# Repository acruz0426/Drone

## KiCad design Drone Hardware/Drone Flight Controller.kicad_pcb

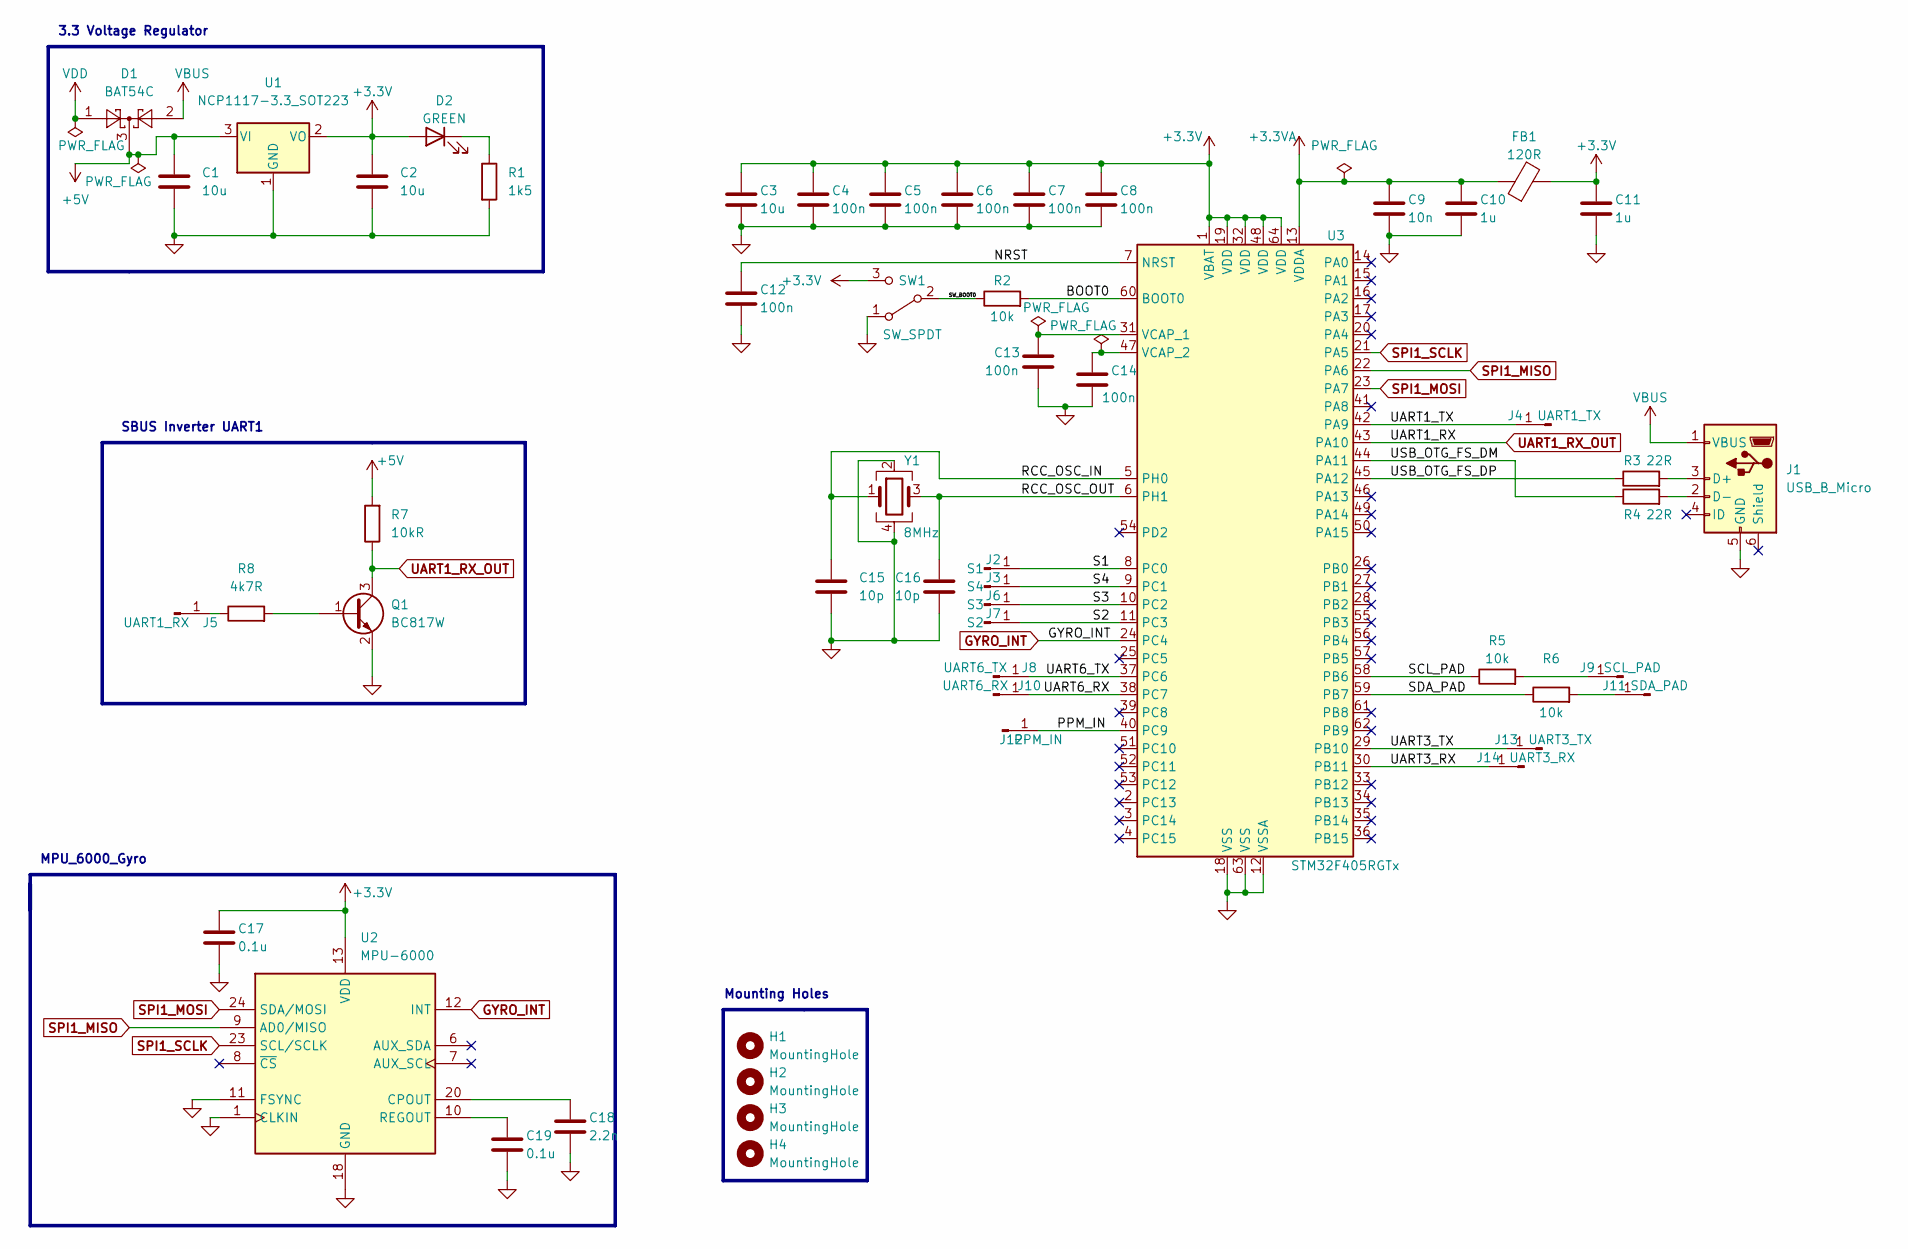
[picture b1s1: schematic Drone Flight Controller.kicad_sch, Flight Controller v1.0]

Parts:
C1, C2, C3: 10u; C_0805_2012Metric
C4, C5, C6, C7, C8, C12, C13, C14: 100n; C_0402_1005Metric
C9: 10n; C_0402_1005Metric
C10, C11: 1u; C_0402_1005Metric
C15, C16: 10p; C_0402_1005Metric
C17, C19: 0.1u; C_0402_1005Metric
C18: 2.2n; C_0402_1005Metric
D1: BAT54C; SOT-23
D2: GREEN; LED_0603_1608Metric
FB1: 120R; L_0603_1608Metric
H1, H2, H3, H4: MountingHole; MountingHole_2.2mm_M2
J1: USB_B_Micro; USB_Micro-B_Wuerth_629105150521
J2: S1; SolderWirePad_1x01_SMD_1x2mm
J3: S4; SolderWirePad_1x01_SMD_1x2mm
J4: UART1_TX; SolderWirePad_1x01_SMD_1x2mm
J5: UART1_RX; SolderWirePad_1x01_SMD_1x2mm
J6: S3; SolderWirePad_1x01_SMD_1x2mm
J7: S2; SolderWirePad_1x01_SMD_1x2mm
J8: UART6_TX; SolderWirePad_1x01_SMD_1x2mm
J9: SCL_PAD; SolderWirePad_1x01_SMD_1x2mm
J10: UART6_RX; SolderWirePad_1x01_SMD_1x2mm
J11: SDA_PAD; SolderWirePad_1x01_SMD_1x2mm
J12: PPM_IN; SolderWirePad_1x01_SMD_1x2mm
J13: UART3_TX; SolderWirePad_1x01_SMD_1x2mm
J14: UART3_RX; SolderWirePad_1x01_SMD_1x2mm
Q1: BC817W; SOT-323_SC-70
R1: 1k5; R_0402_1005Metric
R2, R5, R6: 10k; R_0402_1005Metric
R3, R4: 22R; R_0402_1005Metric
R7: 10kR; R_0402_1005Metric
R8: 4k7R; R_0402_1005Metric
SW1: SW_SPDT; SW_DIP_SPSTx01_Slide_Copal_CVS-01xB_W5.9mm_P1mm
U1: NCP1117-3.3_SOT223; SOT-223-3_TabPin2
U2: MPU-6000; InvenSense_QFN-24_4x4mm_P0.5mm
U3: STM32F405RGTx; LQFP-64_10x10mm_P0.5mm
Y1: 8MHz; Crystal_SMD_3225-4Pin_3.2x2.5mm

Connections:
+3.3V: C2.1, C3.1, C4.1, C5.1, C6.1, C7.1, C8.1, C11.1, C17.1, D2.2 (A), FB1.2, SW1.3 (C), U1.2 (VO), U2.13 (VDD), U3.1 (VBAT), U3.19 (VDD), U3.32 (VDD), U3.48 (VDD), U3.64 (VDD)
+3.3VA: C9.1, C10.1, FB1.1, U3.13 (VDDA)
/BOOT0: R2.2, U3.60 (BOOT0)
/NRST: C12.1, U3.7 (NRST)
/PPM_IN: J12.1, U3.40 (PC9)
/RCC_OSC_IN: C15.1, U3.5 (PH0), Y1.1
/RCC_OSC_OUT: C16.1, U3.6 (PH1), Y1.3
/S1: J2.1, U3.8 (PC0)
/S2: J7.1, U3.11 (PC3)
/S3: J6.1, U3.10 (PC2)
/S4: J3.1, U3.9 (PC1)
/SCL_PAD: R5.1, U3.58 (PB6)
/SDA_PAD: R6.1, U3.59 (PB7)
/SW_BOOT0: R2.1, SW1.2 (B)
/UART1_TX: J4.1, U3.42 (PA9)
/UART3_RX: J14.1, U3.30 (PB11)
/UART3_TX: J13.1, U3.29 (PB10)
/UART6_RX: J10.1, U3.38 (PC7)
/UART6_TX: J8.1, U3.37 (PC6)
/USB_OTG_FS_DM: R4.1, U3.44 (PA11)
/USB_OTG_FS_DP: R3.1, U3.45 (PA12)
GND: C1.2, C2.2, C3.2, C4.2, C5.2, C6.2, C7.2, C8.2, C9.2, C10.2, C11.2, C12.2, C13.2, C14.2, C15.2, C16.2, C17.2, C18.2, C19.2, J1.5 (GND), Q1.2 (E), R1.2, SW1.1 (A), U1.1 (GND), U2.1 (CLKIN), U2.11 (FSYNC), U2.18 (GND), U3.12 (VSSA), U3.18 (VSS), U3.63 (VSS), Y1.2, Y1.4
GYRO_INT: U2.12 (INT), U3.24 (PC4)
unnamed: C13.1, U3.31 (VCAP_1)
unnamed: C14.1, U3.47 (VCAP_2)
unnamed: C18.1, U2.20 (CPOUT)
unnamed: C19.1, U2.10 (REGOUT)
unnamed: D2.1 (K), R1.1
unnamed: J1.2 (D-), R4.2
unnamed: J1.3 (D+), R3.2
unnamed: J5.1, R8.1
unnamed: J9.1, R5.2
unnamed: J11.1, R6.2
unnamed: Q1.1 (B), R8.2
SPI1_MISO: U2.9 (AD0/MISO), U3.22 (PA6)
SPI1_MOSI: U2.24 (SDA/MOSI), U3.23 (PA7)
SPI1_SCLK: U2.23 (SCL/SCLK), U3.21 (PA5)
UART1_RX_OUT: Q1.3 (C), R7.1, U3.43 (PA10)
VBUS: D1.2, J1.1 (VBUS)
VDD: D1.1

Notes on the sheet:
MPU_6000_Gyro
3.3 Voltage Regulator
SBUS Inverter UART1
Mounting Holes

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
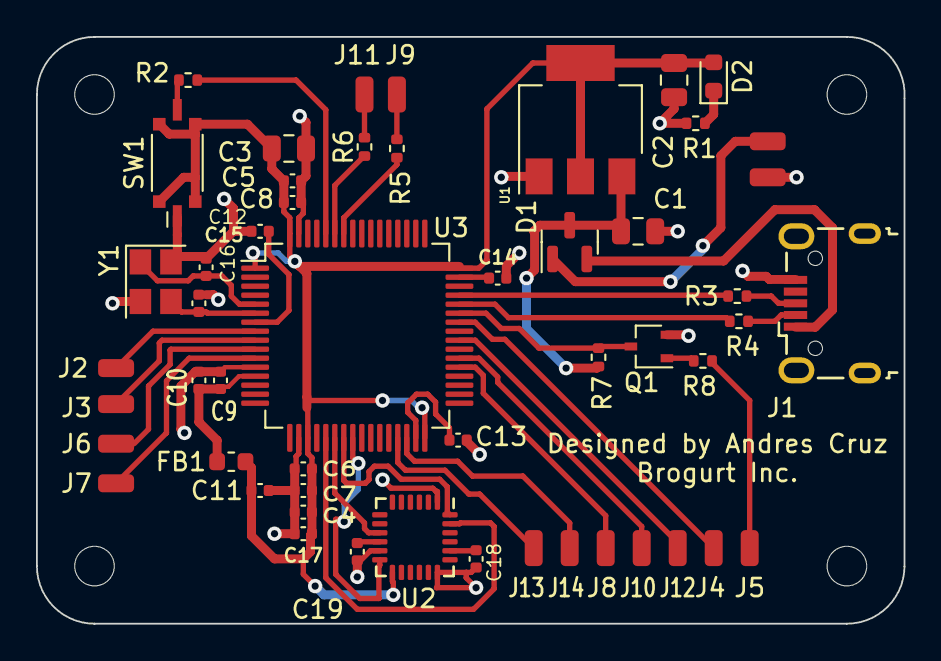
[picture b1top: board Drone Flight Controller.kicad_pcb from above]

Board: 2 copper layers, 48.2 x 32.6 mm, 54 parts (0 on the bottom side), 40 nets.

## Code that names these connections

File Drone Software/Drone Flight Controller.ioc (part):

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Mcu.Name=STM32F405RGTx
Mcu.Package=LQFP64
Mcu.UserName=STM32F405RGTx
PA10.Mode=Asynchronous
PA10.Signal=USART1_RX
PA11.Mode=Device_Only
PA11.Signal=USB_OTG_FS_DM
PA12.Mode=Device_Only
PA12.Signal=USB_OTG_FS_DP
PA13.Mode=Serial_Wire
PA13.Signal=SYS_JTMS-SWDIO
PA14.Mode=Serial_Wire
PA14.Signal=SYS_JTCK-SWCLK
PA2.Signal=GPIO_Output
PA3.Signal=GPIO_Output
PA4.Signal=SPI1_NSS
PA5.Mode=Full_Duplex_Master
PA5.Signal=SPI1_SCK
PA6.Mode=Full_Duplex_Master
PA6.Signal=SPI1_MISO
PA7.Mode=Full_Duplex_Master
PA7.Signal=SPI1_MOSI
PA9.Mode=Asynchronous
PA9.Signal=USART1_TX
PB0.Signal=GPIO_Output
PB1.Signal=GPIO_Output
PB10.Mode=Asynchronous
PB10.Signal=USART3_TX
PB11.Mode=Asynchronous
PB11.Signal=USART3_RX
PB6.Mode=I2C
PB6.Signal=I2C1_SCL
PB7.Mode=I2C
PB7.Signal=I2C1_SDA
PC4.Signal=GPIO_Input
PC6.Mode=Asynchronous
PC6.Signal=USART6_TX
PC7.Mode=Asynchronous
PC7.Signal=USART6_RX
PC9.Signal=GPIO_Input
PH0-OSC_IN.Mode=HSE-External-Oscillator
PH0-OSC_IN.Signal=RCC_OSC_IN
PH1-OSC_OUT.Mode=HSE-External-Oscillator
PH1-OSC_OUT.Signal=RCC_OSC_OUT
RCC.HSE_VALUE=25000000
RCC.SYSCLKFreq_VALUE=16000000
board=custom

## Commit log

2022-07-15 Added Drone software and hardware files to github.
2022-07-16 Basic PCB outline created
2022-07-18 Wired the decoupling capacitors, crystal and USB
2022-07-27 Reconfigured linux repository and finished version 1.0 of the flight controller.
